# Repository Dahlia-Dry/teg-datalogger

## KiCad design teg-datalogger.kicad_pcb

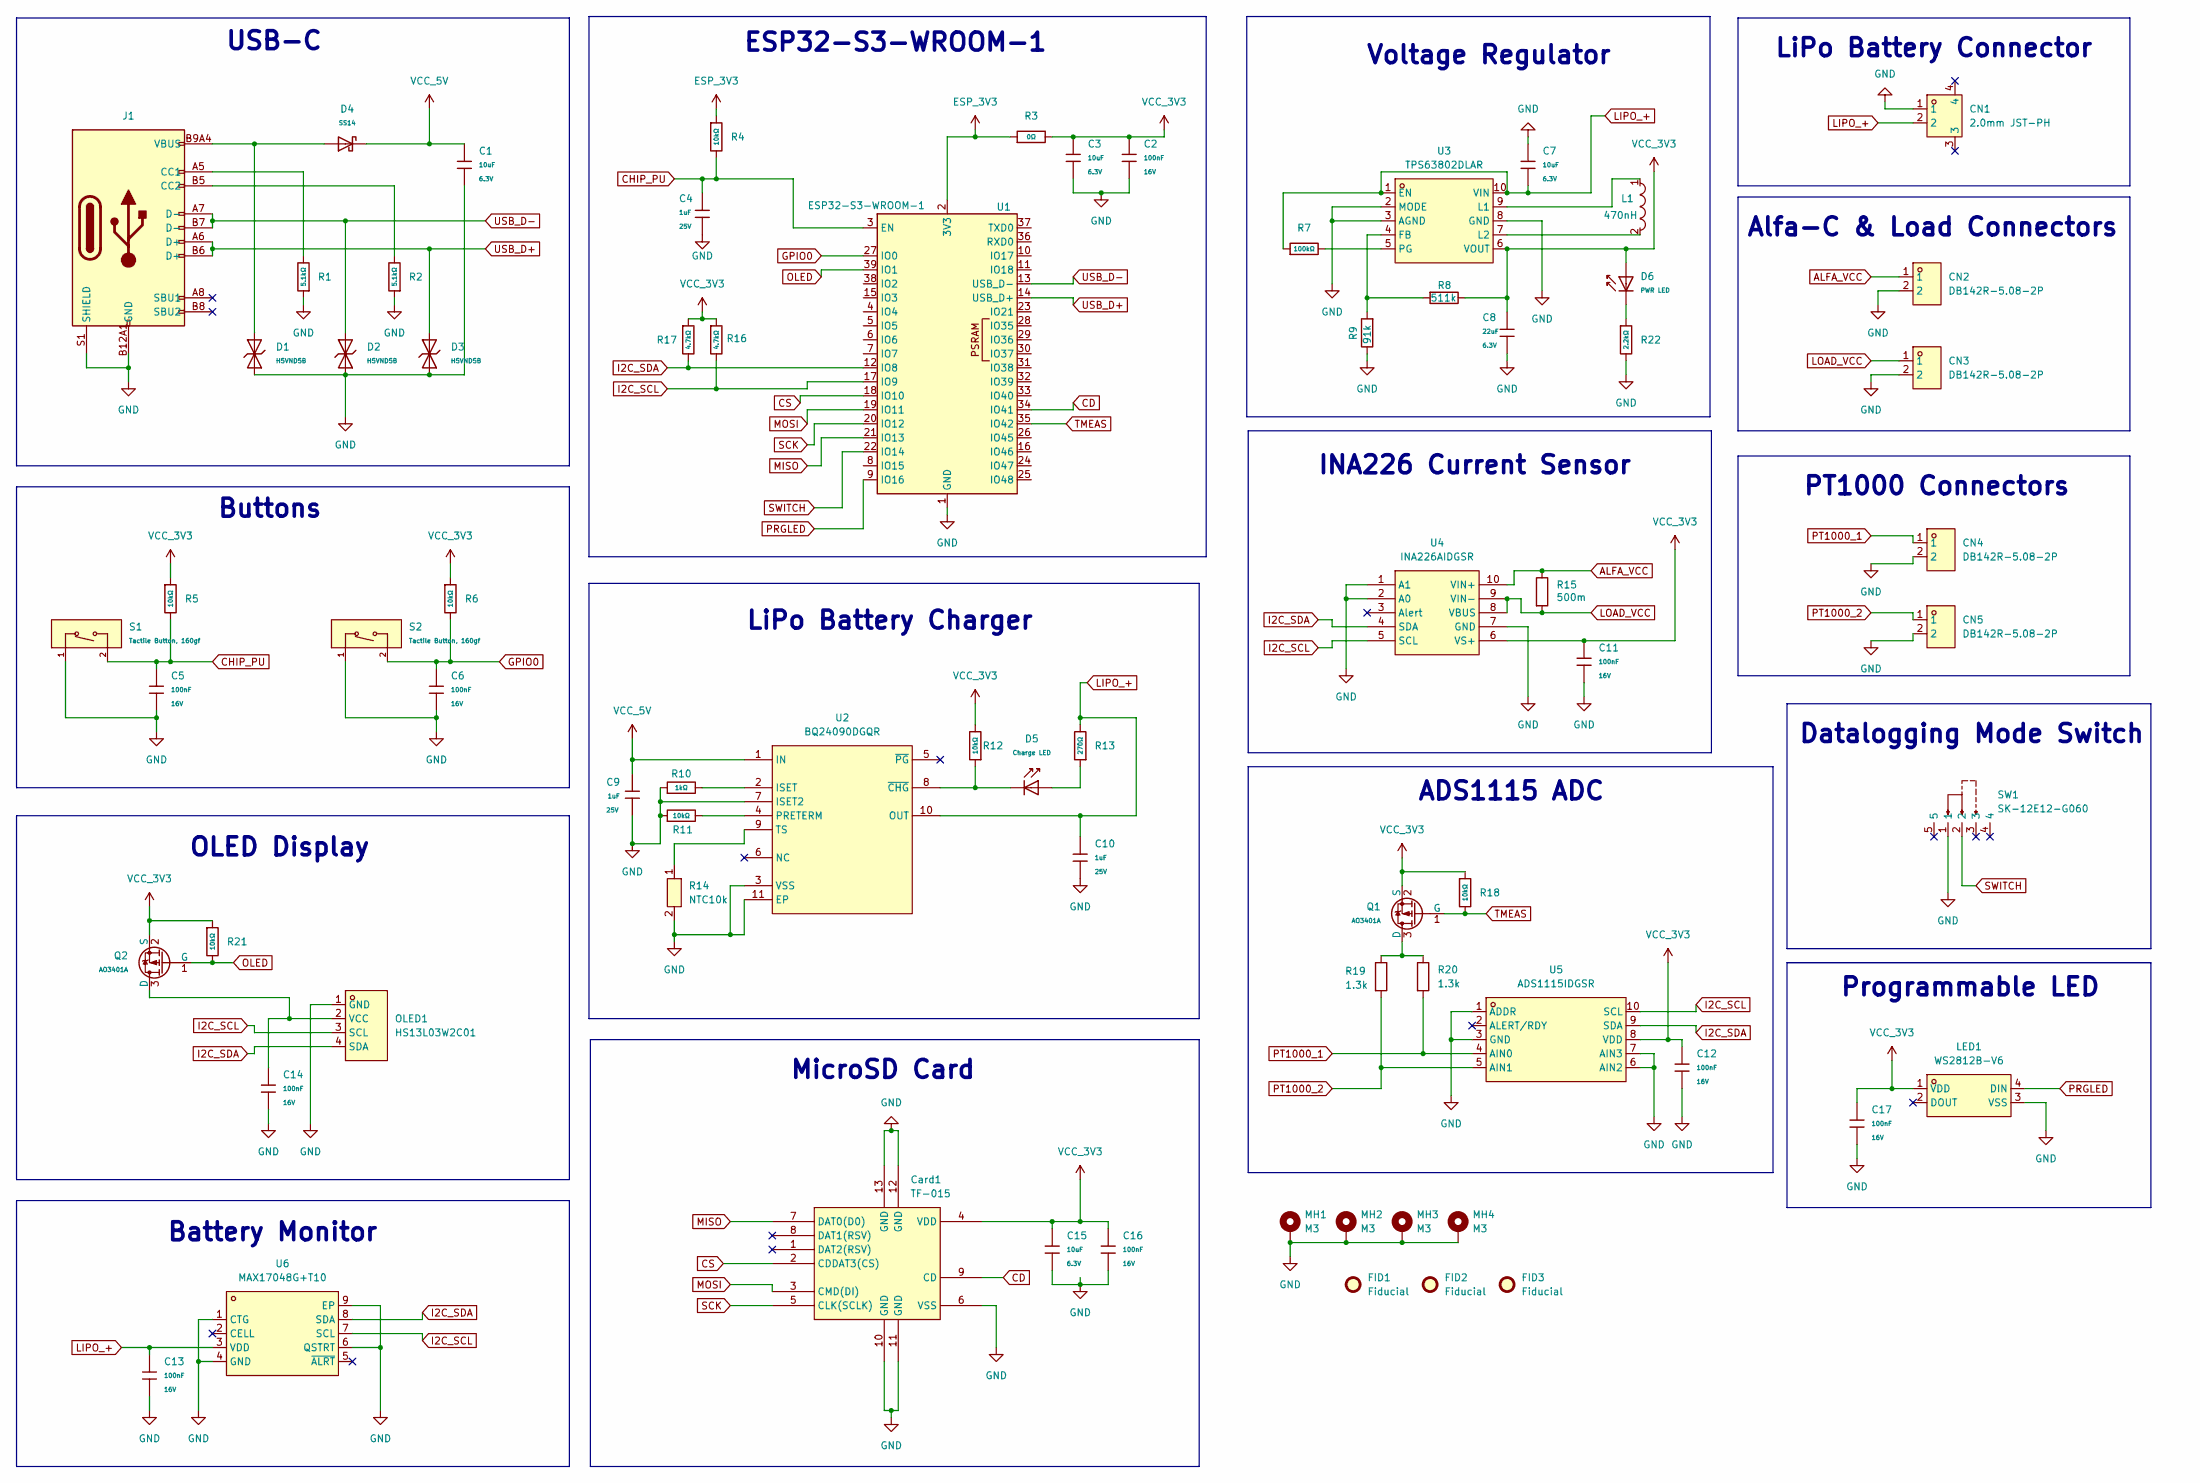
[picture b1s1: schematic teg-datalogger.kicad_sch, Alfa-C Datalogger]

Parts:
C1, C3, C7, C15: 10uF; C_0402; Voltage Rated 6.3V; Tolerance ±20%; Part CL05A106MQ5NUNC; LCSC C15525
C2, C5, C6, C11, C12, C13, C14, C16, C17: 100nF; C_0402; Voltage Rated 16V; Tolerance ±10%; Part CL05B104KO5NNNC; LCSC C1525
C4, C9, C10: 1uF; C_0402; Voltage Rated 25V; Tolerance ±10%; Part CL05A105KA5NQNC; LCSC C52923
C8: 22uF; C_0603; Voltage Rated 6.3V; Tolerance ±20%; Part CL10A226MQ8NRNC; LCSC C59461
CN1: 2.0mm JST-PH; CONN-SMD_P2.00_S2B-PH-SM4-TB-LF-SN; MPN S2B-PH-SM4-TB(LF)(SN); LCSC Part C295747
CN2, CN3, CN4, CN5: DB142R-5.08-2P; CONN-TH_2P-P5.08_DIBO_DB142R-5.08-2P; MPN DB142R-5.08-2P-GN; LCSC C2898709
Card1: TF-015; TF-SMD_TF-015; MPN TF-015; LCSC C113206
D1, D2, D3: H5VND5B; D_SOD-523; Part H5VND5B; LCSC C20615818
D4: SS14; D_SMA; Forward Voltage (Vf@If) 550mV@1A; Reverse Voltage (Vr) 40V; Part SS14; LCSC C2480
D5: Charge LED; D_0805; Forward Voltage (VF) 1.6V~2.6V; Part NCD0805R1; LCSC C84256
D6: PWR LED; D_0805; Forward Voltage (VF) 1.6V~2.6V; Part NCD0805R1; LCSC C84256
FID1, FID2, FID3: Fiducial; Fiducial_1mm_Mask2mm
J1: Connector, USB-TYPE-C-16P; TYPE-C-SMD_HX-TYPE-C-16PIN; LCSC C2927039
L1: 470nH; IND-SMD_L2.5-W2.0_VLS252010HBX; MPN VLS252010HBX-R47M-1; LCSC Part C88530
LED1: WS2812B-V6; LED-SMD_4P-L5.0-W5.0-TL-A; MPN WS2812B-V6; LCSC C52917433
MH1, MH2, MH3, MH4: M3; MountingHole_3.2mm_M3_Pad_Via
OLED1: HS13L03W2C01; OLED-TH_L35.4-W33.5_HS13L03W2C01; MPN HS13L03W2C01; LCSC C7465997
Q1, Q2: AO3401A; Q_SOT-23; Part AO3401A; LCSC C15127
R1, R2: 5.1kΩ; R_0402; Overload Voltage (Max) 50V; Tolerance ±1%; Part 0402WGF5101TCE; LCSC C25905
R3: 0Ω; R_0402; Overload Voltage (Max) 50V; Tolerance ±1%; Part 0402WGF0000TCE; LCSC C17168
R4, R5, R6, R11, R12, R18, R21: 10kΩ; R_0402; Overload Voltage (Max) 50V; Tolerance ±1%; Part 0402WGF1002TCE; LCSC C25744
R7: 100kΩ; R_0402; Overload Voltage (Max) 50V; Tolerance ±1%; Part 0402WGF1003TCE; LCSC C25741
R8: 511k; R_0402; LCSC C5126239
R9: 91k; R_0402; LCSC C60490
R10: 1kΩ; R_0402; Overload Voltage (Max) 50V; Tolerance ±1%; Part 0402WGF1001TCE; LCSC C11702
R13: 270Ω; R_0603; Overload Voltage (Max) 75V; Tolerance ±1%; Part 0603WAF2700T5E; LCSC C22966
R14: NTC10k; R0603; MPN NTCG163JF103HT1; LCSC Part C531304
R15: 500m; R_1206; LCSC C346764
R16, R17: 4.7kΩ; R_0402; Overload Voltage (Max) 50V; Tolerance ±1%; Part 0402WGF4701TCE; LCSC C25900
R19, R20: 1.3k; R_0603; LCSC C860193
R22: 2.2kΩ; R_0402; Overload Voltage (Max) 50V; Tolerance ±1%; Part 0402WGF2201TCE; LCSC C25879
S1, S2: Tactile Button, 160gf; SW_TS-1088-AR02016; Voltage Rating (Dc) 12V; Part TS-1088-AR02016; LCSC C720477
SW1: SK-12E12-G060; SW-TH_SK-12E12-G070; MPN SK-12E12-G060; LCSC C22448008
U1: ESP32-S3-WROOM-1; LCSC C2913202
U2: BQ24090DGQR; MSOP-10_L3.0-W3.0-P0.50-LS5.0-BL-EP; MPN BQ24090DGQR; LCSC C43306
U3: TPS63802DLAR; VSON-10_L3.0-W2.0-P0.50-TL; MPN TPS63802DLAR; LCSC C2845237
U4: INA226AIDGSR; MSOP-10_L3.0-W3.0-P0.50-LS5.0-BL; MPN INA226AIDGSR; LCSC Part C49851
U5: ADS1115IDGSR; MSOP-10_L3.0-W3.0-P0.50-LS5.0-BL; MPN ADS1115IDGSR; LCSC C37593
U6: MAX17048G+T10; TDFN-8_L2.0-W2.0-P0.50-BL-EP1.2; MPN MAX17048G+T10; LCSC C2682616

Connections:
ALFA_VCC: CN2.1, R15.1, U4.10 (VIN+)
CD: Card1.9 (CD), U1.34 (IO41)
CHIP_PU: C4.2, C5.1, R4.2, R5.2, S1.2 (B), U1.3 (EN)
CS: Card1.2 (CDDAT3(CS)), U1.18 (IO10)
ESP_3V3: R3.1, R4.1, U1.2 (3V3)
GND: C1.2, C2.2, C3.2, C4.1, C5.2, C6.2, C7.1, C8.1, C9.2, C10.2, C11.2, C12.2, C13.2, C14.2, C15.2, C16.2, C17.2, CN1.1, CN2.2, CN3.2, CN4.2, CN5.2, Card1.6 (VSS), Card1.10 (GND), Card1.11 (GND), Card1.12 (GND), Card1.13 (GND), D1.1, D2.1, D3.1, J1.A12B1 (GND), J1.B12A1 (GND), J1.S1 (SHIELD), LED1.3 (VSS), MH1.1 (1_1), MH2.1 (1_1), MH3.1 (1_1), MH4.1 (1_1), OLED1.1 (GND), R1.1, R2.1, R9.1, R10.1, R11.1, R14.2, R22.2, S1.1 (A), S2.1 (A), SW1.1, U1.1 (GND), U1.40 (GND), U1.41 (GND), U2.3 (VSS), U2.7 (ISET2), U2.11 (EP), U3.2 (MODE), U3.3 (AGND), U3.8 (GND), U4.1 (A1), U4.2 (A0), U4.7 (GND), U5.1 (ADDR), U5.3 (GND), U5.6 (AIN2), U5.7 (AIN3), U6.1 (CTG), U6.4 (GND), U6.6 (QSTRT), U6.9 (EP)
GPIO0: C6.1, R6.2, S2.2 (B), U1.27 (IO0)
I2C_SCL: OLED1.3 (SCL), R16.2, U1.17 (IO9), U4.5 (SCL), U5.10 (SCL), U6.7 (SCL)
I2C_SDA: OLED1.4 (SDA), R17.2, U1.12 (IO8), U4.4 (SDA), U5.9 (SDA), U6.8 (SDA)
LIPO_+: C7.2, C10.1, C13.1, CN1.2, R7.1, R13.2, U2.10 (OUT), U3.1 (EN), U3.10 (VIN), U6.3 (VDD)
LOAD_VCC: CN3.1, R15.2, U4.8 (VBUS), U4.9 (VIN-)
MISO: Card1.7 (DAT0(D0)), U1.21 (IO13)
MOSI: Card1.3 (CMD(DI)), U1.19 (IO11)
unnamed: D1.2, D4.2, J1.A9B4 (VBUS), J1.B9A4 (VBUS)
unnamed: D5.2, R13.1
unnamed: D6.1, R22.1
unnamed: J1.A5 (CC1), R1.2
unnamed: J1.B5 (CC2), R2.2
unnamed: C14.1, OLED1.2 (VCC), Q2.3 (D)
unnamed: Q1.3 (D), R19.1, R20.1
unnamed: R10.2, U2.2 (ISET)
unnamed: R11.2, U2.4 (PRETERM)
unnamed: R14.1, U2.9 (TS)
unnamed: D5.1, R12.1, U2.8 (~CHG)
unnamed: R8.2, R9.2, U3.4 (FB)
unnamed: L1.1, U3.9 (L1)
unnamed: L1.2, U3.7 (L2)
unnamed: R7.2, U3.5 (PG)
OLED: Q2.1 (G), R21.2, U1.39 (IO1)
PRGLED: LED1.4 (DIN), U1.9 (IO16)
PT1000_1: CN4.1, R20.2, U5.4 (AIN0)
PT1000_2: CN5.1, R19.2, U5.5 (AIN1)
SCK: Card1.5 (CLK(SCLK)), U1.20 (IO12)
SWITCH: SW1.2, U1.22 (IO14)
TMEAS: Q1.1 (G), R18.2, U1.35 (IO42)
USB_D+: D3.2, J1.A6 (D+), J1.B6 (D+), U1.14 (USB_D+)
USB_D-: D2.2, J1.A7 (D-), J1.B7 (D-), U1.13 (USB_D-)
VCC_3V3: C2.1, C3.1, C8.2, C11.1, C12.1, C15.1, C16.1, C17.1, Card1.4 (VDD), D6.2, LED1.1 (VDD), Q1.2 (S), Q2.2 (S), R3.2, R5.1, R6.1, R8.1, R12.2, R16.1, R17.1, R18.1, R21.1, U3.6 (VOUT), U4.6 (VS+), U5.8 (VDD)
VCC_5V: C1.1, C9.1, D4.1, U2.1 (IN)

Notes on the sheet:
Buttons
INA226 Current Sensor
Voltage Regulator
Battery Monitor
PT1000 Connectors
Programmable LED
OLED Display
ESP32-S3-WROOM-1
MicroSD Card
LiPo Battery Connector
LiPo Battery Charger
Datalogging Mode Switch
Alfa-C & Load Connectors
USB-C
ADS1115 ADC

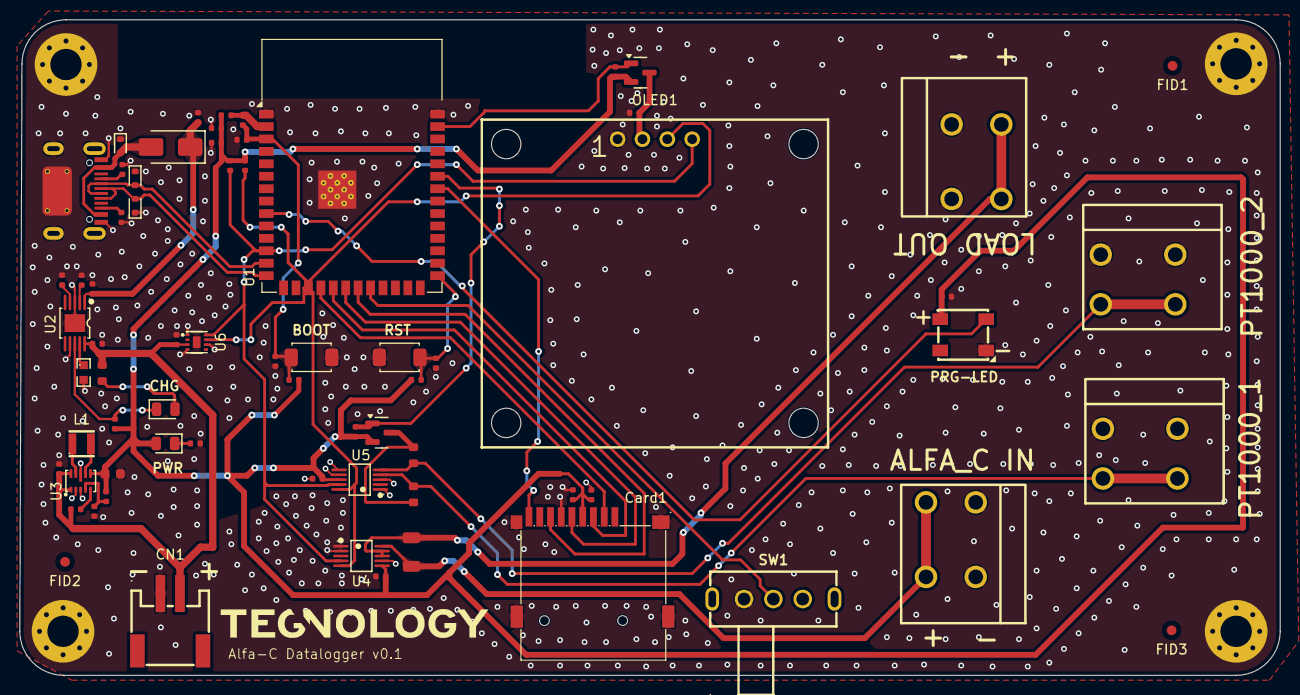
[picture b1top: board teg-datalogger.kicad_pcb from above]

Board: 2 copper layers, 128.8 x 67.0 mm, 73 parts (0 on the bottom side), 39 nets.

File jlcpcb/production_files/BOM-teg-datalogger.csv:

Comment,Designator,Footprint,LCSC,Quantity
0Ω,R3,R_0402,C17168,1
1.3k,"R19,R20",R_0603,C860193,2
100kΩ,R7,R_0402,C25741,1
100nF,"C11,C12,C13,C14,C16,C17,C2,C5,C6",C_0402,C1525,9
10kΩ,"R11,R12,R18,R21,R4,R5,R6",R_0402,C25744,7
10uF,"C1,C15,C3,C7",C_0402,C15525,4
1kΩ,R10,R_0402,C11702,1
1uF,"C10,C4,C9",C_0402,C52923,3
2.0mm JST-PH,CN1,CONN-SMD_P2.00_S2B-PH-SM4-TB-LF-SN,C295747,1
2.2kΩ,R22,R_0402,C25879,1
22uF,C8,C_0603,C59461,1
270Ω,R13,R_0603,C22966,1
4.7kΩ,"R16,R17",R_0402,C25900,2
470nH,L1,IND-SMD_L2.5-W2.0_VLS252010HBX,C88530,1
5.1kΩ,"R1,R2",R_0402,C25905,2
500m,R15,R_1206,C346764,1
511k,R8,R_0402,C5126239,1
91k,R9,R_0402,C60490,1
ADS1115IDGSR,U5,MSOP-10_L3.0-W3.0-P0.50-LS5.0-BL,C37593,1
AO3401A,"Q1,Q2",Q_SOT-23,C15127,2
BQ24090DGQR,U2,MSOP-10_L3.0-W3.0-P0.50-LS5.0-BL-EP,C43306,1
Charge LED,D5,D_0805,C84256,1
"Connector, USB-TYPE-C-16P",J1,TYPE-C-SMD_HX-TYPE-C-16PIN,C2927039,1
DB142R-5.08-2P,"CN2,CN3,CN4,CN5",CONN-TH_2P-P5.08_DIBO_DB142R-5.08-2P,C2898709,4
ESP32-S3-WROOM-1,U1,ESP32-S3-WROOM-1,C2913202,1
H5VND5B,"D1,D2,D3",D_SOD-523,C20615818,3
HS13L03W2C01,OLED1,OLED-TH_L35.4-W33.5_HS13L03W2C01,C7465997,1
INA226AIDGSR,U4,MSOP-10_L3.0-W3.0-P0.50-LS5.0-BL,C49851,1
MAX17048G+T10,U6,TDFN-8_L2.0-W2.0-P0.50-BL-EP1.2,C2682616,1
NTC10k,R14,R0603,C531304,1
PWR LED,D6,D_0805,C84256,1
SK-12E12-G060,SW1,SW-TH_SK-12E12-G070,C22448008,1
SS14,D4,D_SMA,C2480,1
TF-015,Card1,TF-SMD_TF-015,C113206,1
TPS63802DLAR,U3,VSON-10_L3.0-W2.0-P0.50-TL,C2845237,1
"Tactile Button, 160gf","S1,S2",SW_TS-1088-AR02016,C720477,2
WS2812B-V6,LED1,LED-SMD_4P-L5.0-W5.0-TL-A,C52917433,1
Fiducial,FID1,Fiducial_1mm_Mask2mm,,1
